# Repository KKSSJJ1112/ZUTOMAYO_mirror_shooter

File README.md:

# 🔫 Mirror Shooter / ミラーシューター / 미러슈터

> **Language / 言語 / 언어**: [English](#english) | [日本語](#日本語) | [한국어](#한국어)

---

## English

### ZUTOMAYO Mirror Shooter (DIY Replica)

A handmade replica of the mirror shooter prop featured in music videos and live performances by the Japanese J-pop band **ZUTOMAYO** (ずっと真夜中でいいのに。).

This pistol-shaped prop features LED illumination and a laser emitter at the muzzle.

### Features

- 3300mAh lithium-ion battery system
- Modular case design (assembly/disassembly capable)
- 3D printed enclosure
- Reprogrammable (color customization, etc.)
- Physical trigger switch for laser on/off mode toggle

### Components

| Part | Specification |
|------|---------------|
| PCB | Custom designed in KiCad, hand-soldered |
| MCU | ESP32-C3 Super Mini |
| LED Strip | NeoPixel (WS2812B) |
| Slide LED Ring | NeoPixel |
| Battery | Samsung SDI 18650 Li-ion cell |

### Project Structure

```
├── mirror/              # ESP32 PlatformIO project files
├── mirror_Shooter_v2/   # KiCad project files
└── mirrorshooter_stl/   # 3D printable STL files
```

### [Photos ↓](#gallery)

---

## 日本語

### ずっと真夜中でいいのに。ミラーシューター（自作レプリカ）

日本のJ-popバンド「**ずっと真夜中でいいのに。**」（以下、ずとまよ）のMVやライブに登場するミラーシューターを自作しました。

拳銃型の小道具で、LEDによる発光と銃口部分からのレーザー照射が特徴です。

### 主な特徴

- 3300mAhリチウムイオンバッテリーシステム
- 組み立て・分解可能なケース構造
- 3Dプリント製ケース
- 再プログラミング可能（カラー変更など）
- トリガーの物理プッシュスイッチによるレーザーON/OFFモード切替

### 構成部品

| 部品 | 仕様 |
|------|------|
| PCB | KiCadで設計、手はんだ実装 |
| MCU | ESP32-C3 Super Mini |
| LEDストリップ | NeoPixel（WS2812B） |
| スライド背面LEDリング | NeoPixel |
| バッテリー | Samsung SDI 18650 リチウムイオンセル |

### プロジェクト構成

```
├── mirror/              # ESP32 PlatformIOプロジェクトファイル
├── mirror_Shooter_v2/   # KiCadプロジェクトファイル
└── mirrorshooter_stl/   # 3Dプリント用STLファイル
```

### [写真 ↓](#gallery)

---

## 한국어

### 계속 한밤중이면 좋을텐데 미러슈터 (자작)

일본의 J-pop 밴드 **계속 한밤중이면 좋을텐데**(ずっと真夜中でいいのに。, 이하 즈토마요)의 MV 및 라이브에 등장하는 미러슈터를 제작했습니다.

권총형 소품으로, LED를 통한 발광과 총구 부분에서의 레이저가 특징입니다.

### 주요 특징

- 3300mAh 리튬 이온 배터리 시스템
- 조립 및 분해 가능한 케이스 구조
- 3D 프린팅 케이스
- 추후 재프로그래밍 가능 (색상 변경 등)
- 트리거의 물리 푸시 스위치를 통한 레이저 ON/OFF 모드 변경

### 구성 부품

| 부품 | 사양 |
|------|------|
| PCB | KiCad 설계, 핸드 솔더링 |
| MCU | ESP32-C3 Super Mini |
| LED 스트립 | NeoPixel (WS2812B) |
| 슬라이드 후면 LED 링 | NeoPixel |
| 배터리 | Samsung SDI 18650 리튬이온 셀 |

### 프로젝트 구조

```
├── mirror/              # ESP32 PlatformIO 프로젝트 파일
├── mirror_Shooter_v2/   # KiCad 프로젝트 파일
└── mirrorshooter_stl/   # 3D 프린팅용 STL 파일
```

### [사진 ↓](#gallery)

---

## Gallery

<!-- 이미지를 여기에 추가하세요 / Add images here / 画像をここに追加 -->

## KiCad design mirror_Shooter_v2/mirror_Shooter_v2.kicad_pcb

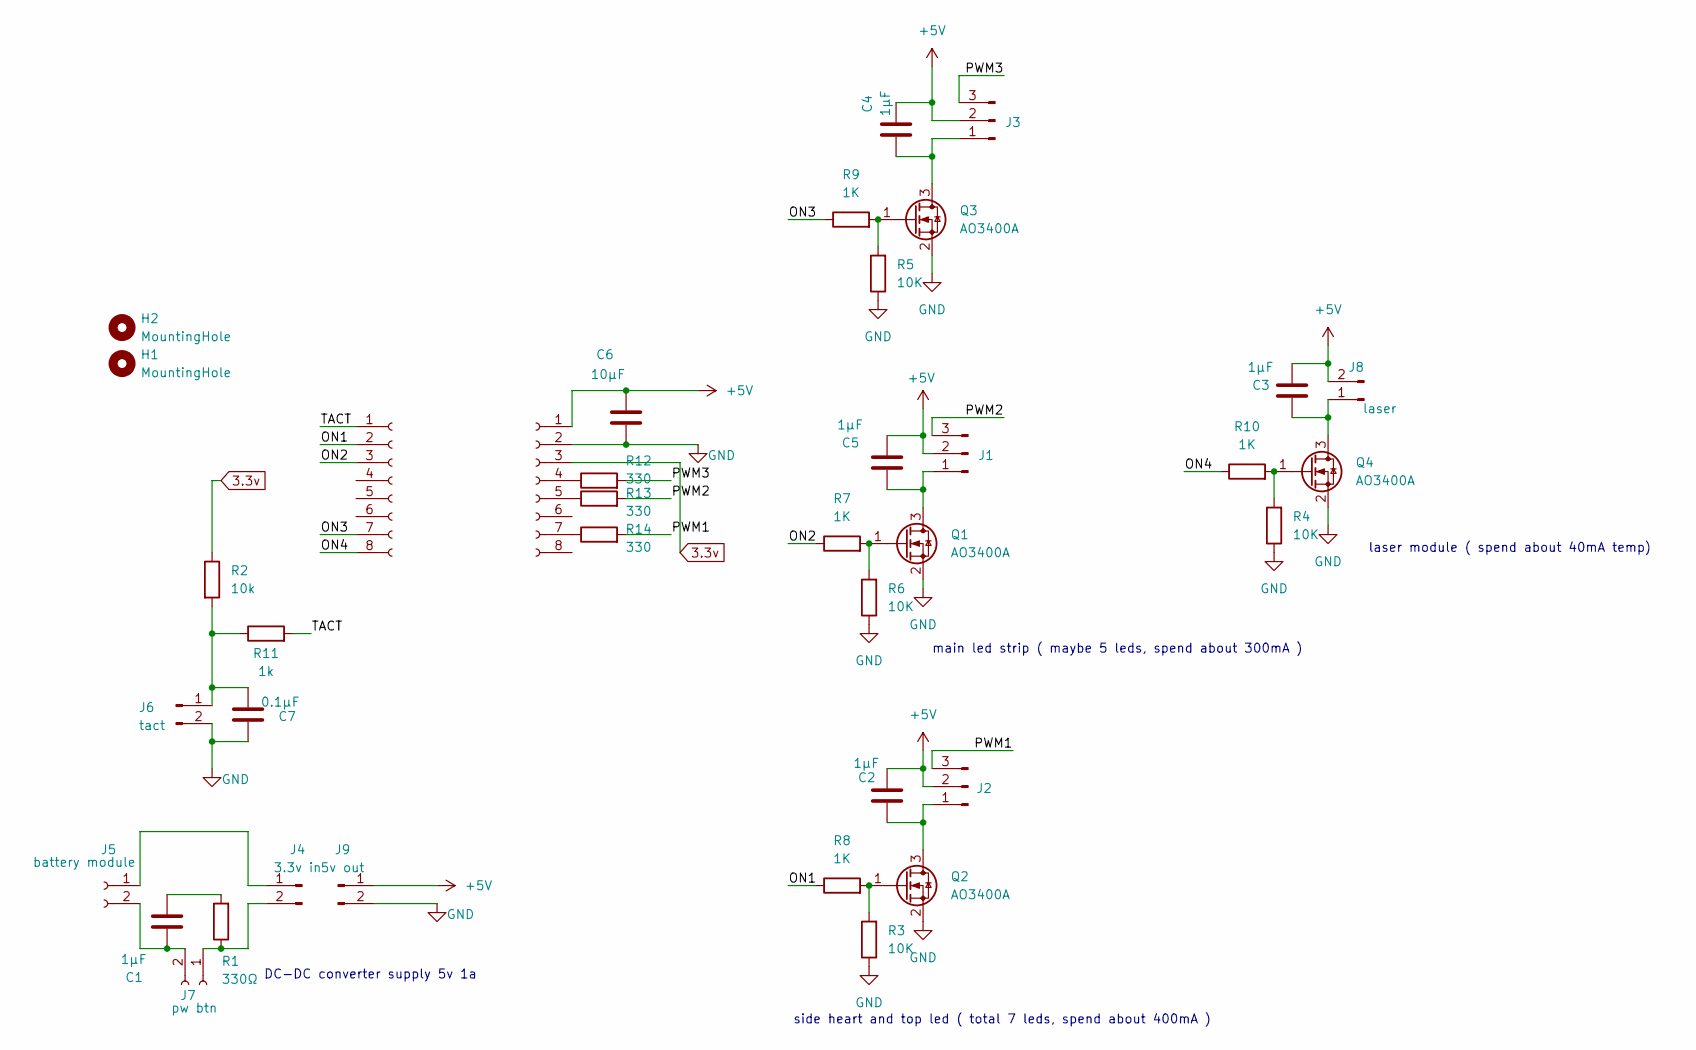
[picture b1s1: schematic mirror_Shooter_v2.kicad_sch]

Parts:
C1, C2, C3, C4, C5: 1μF; C_0603_1608Metric_Pad1.08x0.95mm_HandSolder
C6: 10μF; C_0603_1608Metric_Pad1.08x0.95mm_HandSolder
C7: 0.1μF; C_0603_1608Metric_Pad1.08x0.95mm_HandSolder
H1, H2: MountingHole; MountingHole_3.2mm_M3
J1, J2, J3: Conn_01x03_Pin; JST_XH_B3B-XH-A_1x03_P2.50mm_Vertical
J4: 3.3v in; 제목 없음
J5: battery module; JST_XH_B2B-XH-A_1x02_P2.50mm_Vertical
J6: tact; JST_XH_B2B-XH-A_1x02_P2.50mm_Vertical
J7: pw btn; JST_XH_B2B-XH-A_1x02_P2.50mm_Vertical
J8: laser; JST_XH_B2B-XH-A_1x02_P2.50mm_Vertical
J9: 5v out; stepup in
J10, J11: Conn_01x08_Socket; PinHeader_1x08_P2.54mm_Vertical
Q1, Q2, Q3, Q4: AO3400A; SOT-23
R1: 330Ω; C_0603_1608Metric_Pad1.08x0.95mm_HandSolder
R2: 10k; C_0603_1608Metric_Pad1.08x0.95mm_HandSolder
R3, R4, R5, R6: 10K; C_0603_1608Metric_Pad1.08x0.95mm_HandSolder
R7, R8, R9, R10: 1K; C_0603_1608Metric_Pad1.08x0.95mm_HandSolder
R11: 1k; C_0603_1608Metric_Pad1.08x0.95mm_HandSolder
R12, R13, R14: 330; C_0603_1608Metric_Pad1.08x0.95mm_HandSolder

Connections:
3.3v: J10.3, R2.1
+5V: C2.1, C3.1, C4.1, C5.1, C6.1, J1.2, J2.2, J3.2, J8.2, J9.1, J10.1
/ON1: J11.2, R8.1
/ON2: J11.3, R7.1
/ON3: J11.7, R9.1
/ON4: J11.8, R10.1
/PWM1: J2.3, R14.2
/PWM2: J1.3, R13.2
/PWM3: J3.3, R12.2
/TACT: J11.1, R11.2
GND: C6.2, C7.2, J6.2, J9.2, J10.2, Q1.2 (S), Q2.2 (S), Q3.2 (S), Q4.2 (S), R3.1, R4.1, R5.1, R6.1
unnamed: C1.2, R1.2
unnamed: C5.2, J1.1, Q1.3 (D)
unnamed: C2.2, J2.1, Q2.3 (D)
unnamed: C4.2, J3.1, Q3.3 (D)
unnamed: J4.1, J5.1
unnamed: J4.2, J7.1, R1.1
unnamed: C1.1, J5.2, J7.2
unnamed: C7.1, J6.1, R2.2, R11.1
unnamed: C3.2, J8.1, Q4.3 (D)
unnamed: J10.4, R12.1
unnamed: J10.5, R13.1
unnamed: J10.7, R14.1
unnamed: Q1.1 (G), R6.2, R7.2
unnamed: Q2.1 (G), R3.2, R8.2
unnamed: Q3.1 (G), R5.2, R9.2
unnamed: Q4.1 (G), R4.2, R10.2

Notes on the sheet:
DC-DC converter supply 5v 1a
main led strip ( maybe 5 leds, spend about 300mA )
laser module ( spend about 40mA temp)
side heart and top led ( total 7 leds, spend about 400mA )

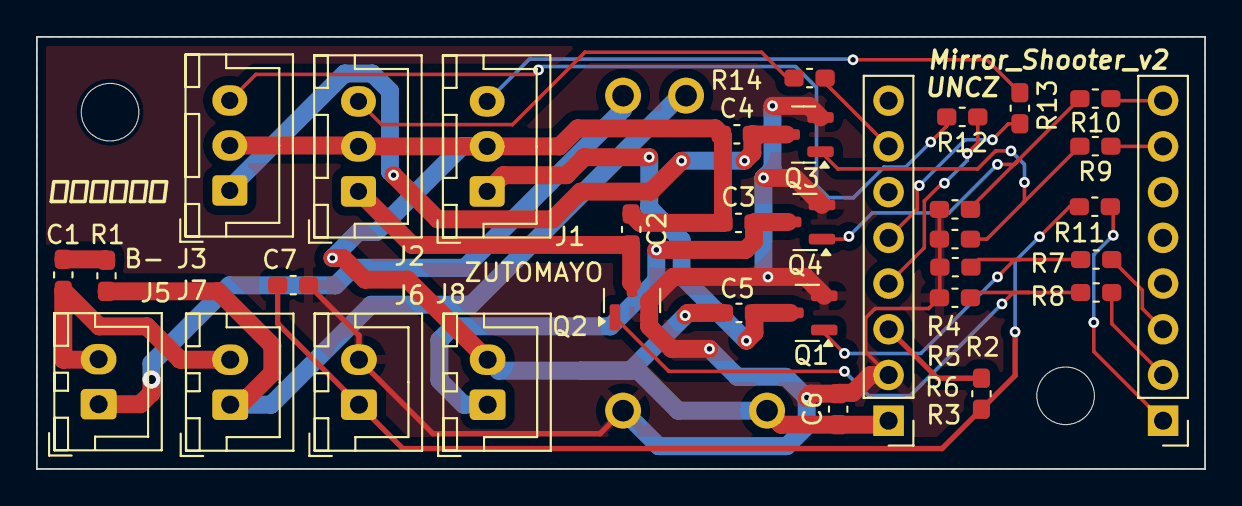
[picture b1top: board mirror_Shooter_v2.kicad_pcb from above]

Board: 2 copper layers, 64.9 x 24.0 mm, 38 parts (0 on the bottom side), 27 nets.

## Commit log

2025-11-05 Save to github
2025-12-31 Add images to the gallery in README
    Added two new images to the gallery section.
